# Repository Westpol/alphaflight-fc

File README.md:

# alphaflight-fc
Schematics, PCB and gerber files for my model aircraft flight controller

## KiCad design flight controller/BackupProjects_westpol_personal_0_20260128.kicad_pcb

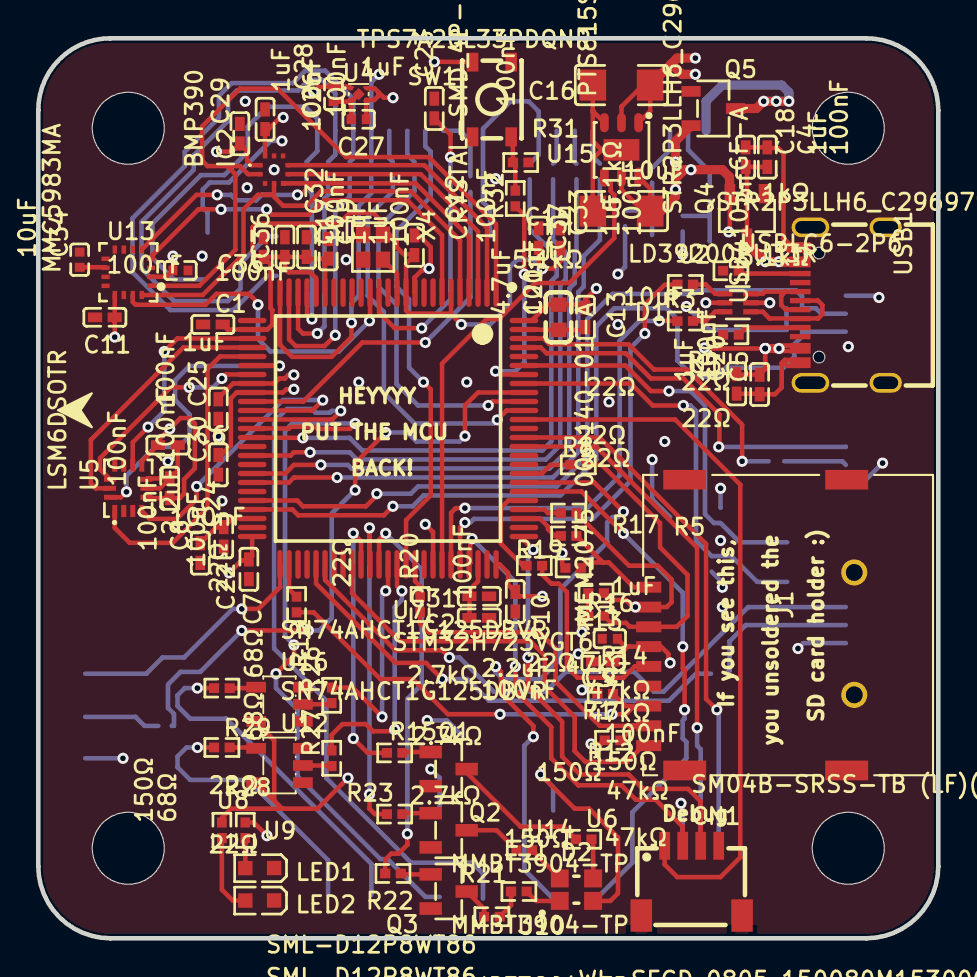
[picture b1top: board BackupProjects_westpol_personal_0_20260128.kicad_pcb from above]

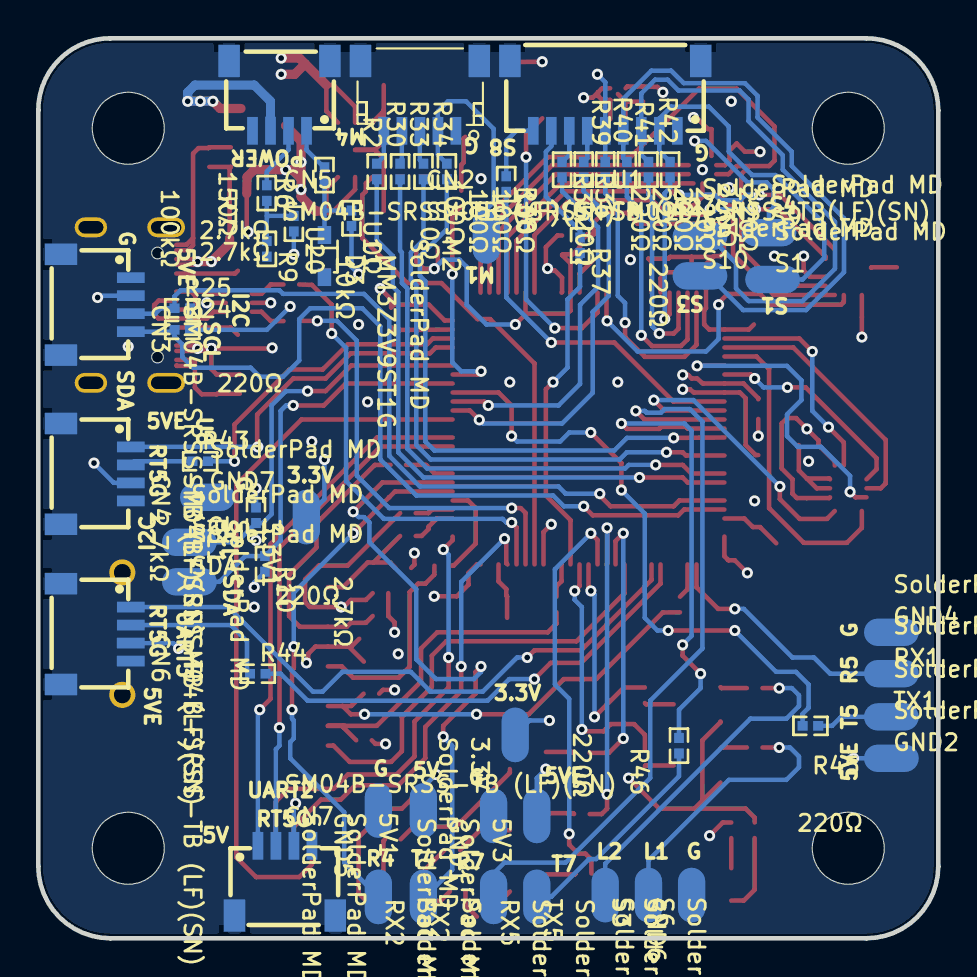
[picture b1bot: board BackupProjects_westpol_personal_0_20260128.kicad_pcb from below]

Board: 4 copper layers, 50.0 x 50.0 mm, 150 parts (58 on the bottom side), 124 nets.

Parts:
3.3V, 3.3V1, 5V1, 5V3: SolderPad MD; SOLDERPAD MD
C1, C2, C3, C4, C5, C6, C7, C8, C10, C11, C12, C13, C23, C24, C25, C28, C29, C30, C32, C36, C37: 100nF; C0402
C9, C17, C18, C19, C20, C26, C27, C33, C35: 1uF; C0402
C15, C16: 10uF; C1206
C21: 4.7uF; C0603
C22, C31: 2.2uF; C0402
C34: 10uF; C0402
CN1, CN3, CN4, CN5, CN6, CN7: SM04B-SRSS-TB (LF)(SN); CONN-SMD_4P-P1.00_SM04B-SRSS-TB-LF-SN
CN2: SM05B-SRSS-TB (LF)(SN); CONN-SMD_SM05B-SRSS-TB-LF-SN
D1: USBLC6-2P6; SOT-666-6_L1.6-W1.2-P0.50-LS1.6-BR
D2: WL-SFCD_0805_150080M153000; WL-SFCX_0805
D3: MM3Z3V9ST1G; SOD-323_L1.8-W1.3-LS2.5-RD
GND1, GND2, GND4, GND5, GND6, GND7: SolderPad MD; SOLDERPAD MD
Hole_gge1082: Hole_gge1082
Hole_gge1112: Hole_gge1112
Hole_gge1127: Hole_gge1127
Hole_gge1142: Hole_gge1142
IC2: BMP390
J1: MEM2075-00-140-01-A; MEM2075-00-140-01-A_GCT
LED1, LED2: SML-D12P8WT86; LED0603-RD_GREEN
M2: SolderPad MD; SOLDERPAD MD
Q1, Q2, Q3: MMBT3904-TP; SOT-23-3_L2.9-W1.3-P1.90-LS2.4-BR
Q4, Q5: STR2P3LLH6_C2969791; SOT-23-3_L2.9-W1.7-P1.90-LS2.8-BR
R1, R12, R13, R14, R16: 47kΩ; R0402
R2, R30, R33, R34: 100Ω; R0402
R3, R4, R5, R8, R17, R18, R19, R20, R28, R29: 22Ω; R0402
R6: 150Ω; R0402
R7: 100kΩ; R0402
R9: 10kΩ; R0402
R10, R11, R15, R22, R23, R24, R25: 2.7kΩ; R0402
R21, R26, R27: 68Ω; R0402
R31, R32: 5.1kΩ; R0402
R35, R36, R37, R38, R39, R40, R41, R42, R43, R44, R45, R46: 220Ω; R0402
RX1, RX2, RX5: SolderPad MD; SOLDERPAD MD
S1, S2, S3, S6, S9, S10: SolderPad MD; SOLDERPAD MD
SCL: SolderPad MD; SOLDERPAD MD
SDA: SolderPad MD; SOLDERPAD MD
SW1: PTS815SJM250SMTRLFS; KEY-SMD_4P-L4.2-W3.25-P2.15-TL
TX1, TX2, TX5: SolderPad MD; SOLDERPAD MD
U1: SM09B-SRSS-TB(LF)(SN); CONN-SMD_SM09B-SRSS-TB-LF-SN
U2, U3: 5.1kΩ; R0402
U4: TPS7A20L33PDQNR; X2SON-4_L1.0-W1.0-P0.65-TL-EP
U5: LSM6DSOTR; LGA-14_L3.0-W2.5-P0.50-TL
U6, U8, U10, U14: 150Ω; R0402
U7: STM32H723VGT6; LQFP-100_L14.0-W14.0-P0.50-LS16.0-BL
U9: 68Ω; R0402
U11, U20: 0Ω; R0402
U12, U16: SN74AHCT1G125DBVR; SOT-23-5_L3.0-W1.7-P0.95-LS2.8-BR
U13: MMC5983MA; LGA-16_L3.0-W3.0-P0.50-BL_SQ
U15: LD39200PU33R; DFN-6_L3.0-W3.0-P0.95-BL-EP
USB1: USB4105-GF-A; TYPE-C-SMD_SBC-160S1A-20-S412
X4: CRYSTAL-SMD_4P-L2.0-W1.6-BL

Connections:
5V_EXT: 5V3.1, CN3.2, CN4.3, CN5.3, CN6.3, GND2.1, Q5.3, R24.2, R25.2
+5V: 5V1.1, C15.1, C27.2, CN7.3, D1.5, D2.4, Q4.2, Q5.2, U4.3, U4.4, U8.2, U12.5, U15.5, U15.6, U16.5
BARO_CS: IC2.6, U7.3
BARO_EXTI: IC2.7, U7.2
BOOT0: R32.2, U7.94
CPU_CLK: U7.12, X4.3
CUR_SENSE: C30.2, U7.34, U11.2
CUR_SENSE_PAD: CN5.1, R6.2
D1_4: D1.4, R3.1
D1_6: D1.6, R4.1
D2_1: D2.1, R21.1
D2_2: D2.2, U14.2
D2_3: D2.3, U6.2
D3_1: D3.1, R6.1, U11.1
GND: C1.1, C2.1, C3.2, C4.1, C5.1, C6.1, C7.1, C8.1, C9.1, C10.1, C11.1, C12.1, C13.1, C15.2, C16.2, C17.1, C18.1, C19.1, C20.1, C21.1, C22.1, C23.1, C24.2, C25.1, C26.1, C27.1, C28.1, C29.1, C30.1, C31.1, C32.1, C33.1, C34.2, C35.1, C36.1, C37.1, CN1.4, CN1.5, CN1.6, CN2.1, CN2.6, CN2.7, CN3.1, CN3.5, CN3.6, CN4.4, CN4.5, CN4.6, CN5.4, CN5.5, CN5.6, CN6.4, CN6.5, CN6.6, CN7.4, CN7.5, CN7.6, D1.2, D3.2, GND1.1, GND4.1, GND5.1, GND6.1, GND7.1, IC2.3, IC2.8, IC2.9, J1.P6, LED1.1, LED2.1, Q1.2, Q2.2, Q3.2, Q4.1, Q5.1, R9.2, R31.1, U1.1, U1.10, U1.11, U2.1, U3.1, U4.2, U4.5, U5.6, U5.7, U7.10, U7.19, U7.26, U7.49, U7.74, U7.99, U12.1, U12.3, U13.9, U13.11, U15.3, U15.7, U16.1, U16.3, USB1.1, USB1.A1, USB1.A12, USB1.B1, USB1.B12, X4.2
I2C1_SCL: R11.1, SCL.1, U7.95
I2C1_SDA: R10.1, SDA.1, U7.93
I2C2_SCL: CN3.3, R25.1, U7.46
I2C2_SDA: CN3.4, R24.1, U7.47
IMU_CS: U5.12, U7.32
IMU_EXTI_1: U5.4, U7.36
IMU_EXTI_2: U5.9, U7.28
J1_P1: J1.P1, R16.1, R19.2
J1_P2: J1.P2, R5.2, R13.1
J1_P3: J1.P3, R8.2, R14.1
J1_P5: J1.P5, R17.1
J1_P7: J1.P7, R1.1, R18.1
J1_P8: J1.P8, R12.1, R20.1
LED1_2: LED1.2, U9.1
LED2_2: LED2.2, U8.1
LED_1: R26.2, U7.63
LED_2: R27.2, U7.64
MAGNETO_CS: U7.7, U13.4
MAGNETO_EXTI: U7.15, U13.15
MOTOR_1: R34.2, U7.39
MOTOR_1_PROTECTED: CN2.2, M2.1, R34.1
MOTOR_2: R33.2, U7.41
MOTOR_2_PROTECTED: CN2.3, R33.1
MOTOR_3: R30.2, U7.43
MOTOR_3_PROTECTED: CN2.4, R30.1
MOTOR_4: R2.2, U7.44
MOTOR_4_PROTECTED: CN2.5, R2.1
NRST: C23.2, U7.14
POWER_GOOD: U7.69, U15.4
Q1_1: Q1.1, R15.2
Q1_3: Q1.3, U6.1
Q2_1: Q2.1, R23.2
Q3_1: Q3.1, R22.2
R9_1: R7.1, R9.1, U20.1
R21_2: R21.2, U10.2
RGB_B: R15.1, U7.60
RGB_G: R23.1, U7.61
RGB_R: R22.1, U7.62
S3_1: R29.2, S3.1
S6_1: R28.2, S6.1
SDMMC1_CK: R17.2, U7.80
SDMMC1_CMD: R8.1, U7.83
SDMMC1_D0: R18.2, U7.52
SDMMC1_D1: R20.2, U7.66
SDMMC1_D2: R19.1, U7.78
SDMMC1_D3: R5.1, U7.79
SD_CARD_DETECT: J1.P9, U7.59
SENSOR_POWER: C6.2, C11.2, C24.1, C26.2, C28.2, C29.2, C35.2, IC2.1, IC2.10, U4.1, U5.5, U5.8, U13.2, U13.13
SERVO_1: R42.2, U7.22
SERVO_1_PROTECTED: R42.1, S1.1, U1.2
SERVO_2: R41.2, U7.23
SERVO_2_PROTECTED: R41.1, S2.1, U1.3
SERVO_3: R40.2, U7.24
SERVO_3_PROTECTED: R40.1, S10.1, U1.4
SERVO_4: R39.2, U7.25
SERVO_4_PROTECTED: R39.1, S9.1, U1.5
SERVO_5: R36.2, U7.90
SERVO_5_PROTECTED: R36.1, U1.6
SERVO_6: R35.2, U7.91
SERVO_6_PROTECTED: R35.1, U1.7
SERVO_7: R37.2, U7.65
SERVO_7_PROTECTED: R37.1, U1.8
SERVO_8: R38.2, U7.35
SERVO_8_PROTECTED: R38.1, U1.9
SPI1_MISO: U5.1, U7.30
SPI1_MOSI: U5.14, U7.31
SPI1_SCK: U5.13, U7.29
SPI4_MISO: IC2.5, U7.4, U13.5
SPI4_MOSI: IC2.4, U7.5, U13.16
SPI4_SCK: IC2.2, U7.1, U13.1
SW1_2: R31.2, R32.1, SW1.2
SWDCLK: CN1.3, U7.76
SWDIO: CN1.2, U7.72
SWO: CN1.1, U7.89
U10_1: Q3.3, U10.1
U12_2: R27.1, U12.2
U12_4: R28.1, U12.4
U13_10: C34.1, U13.10
U14_1: Q2.3, U14.1
U16_2: R26.1, U16.2
U16_4: R29.1, U16.4
UART2_RX: CN7.1, U7.87
UART2_TX: CN7.2, U7.86
UART3_RX: CN6.1, U7.56
UART3_TX: R44.2, U7.55
UART3_TX_PROTECTED: CN6.2, R44.1
UART4_RX: RX2.1, U7.81
UART4_TX: TX2.1, U7.82
UART5_RX: RX1.1, U7.51
UART5_TX: R45.2, U7.92
UART5_TX_PROTECTED: R45.1, TX1.1
UART7_RX: RX5.1, U7.37
UART7_TX: R46.2, U7.38
UART7_TX_PROTECTED: R46.1, TX5.1
UART8_RX: CN4.1, U7.97
UART8_TX: R43.2, U7.98
UART8_TX_PROTECTED: CN4.2, R43.1
USB1_A5: U3.2, USB1.A5
USB1_B5: U2.2, USB1.B5
USB_5V: C4.2, C5.2, C18.2, C20.2, Q4.3, U7.68, USB1.A4, USB1.A9, USB1.B4, USB1.B9
USB_CON_D+: D1.3, USB1.A6, USB1.B6
USB_CON_D-: D1.1, USB1.A7, USB1.B7
USB_D+: R3.2, U7.71
USB_D-: R4.2, U7.70
VBAT_SENSE: C25.2, U7.33, U20.2
VBAT_SENSE_PAD: CN5.2, R7.2
VCAP_1: C8.2, C22.2, U7.48
VCAP_2: C2.2, C31.2, U7.73
VCC: 3.3V.1, 3.3V1.1, C1.2, C3.1, C7.2, C9.2, C10.2, C12.2, C13.2, C16.1, C17.2, C19.2, C21.2, C32.2, C33.2, C36.2, C37.2, J1.P4, R1.2, R10.2, R11.2, R12.2, R13.2, R14.2, R16.2, SW1.3, U7.6, U7.11, U7.20, U7.21, U7.27, U7.50, U7.75, U7.100, U9.2, U15.1, U15.2, X4.4

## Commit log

2026-01-28 Imported EasyEDA to KiCAD
2026-01-28 uploaded EasyEDA gerber
2026-01-28 Updated gerbers

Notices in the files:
parts and their libraries:
Copyright 2021 Accelerated Designs. All rights reserved.
